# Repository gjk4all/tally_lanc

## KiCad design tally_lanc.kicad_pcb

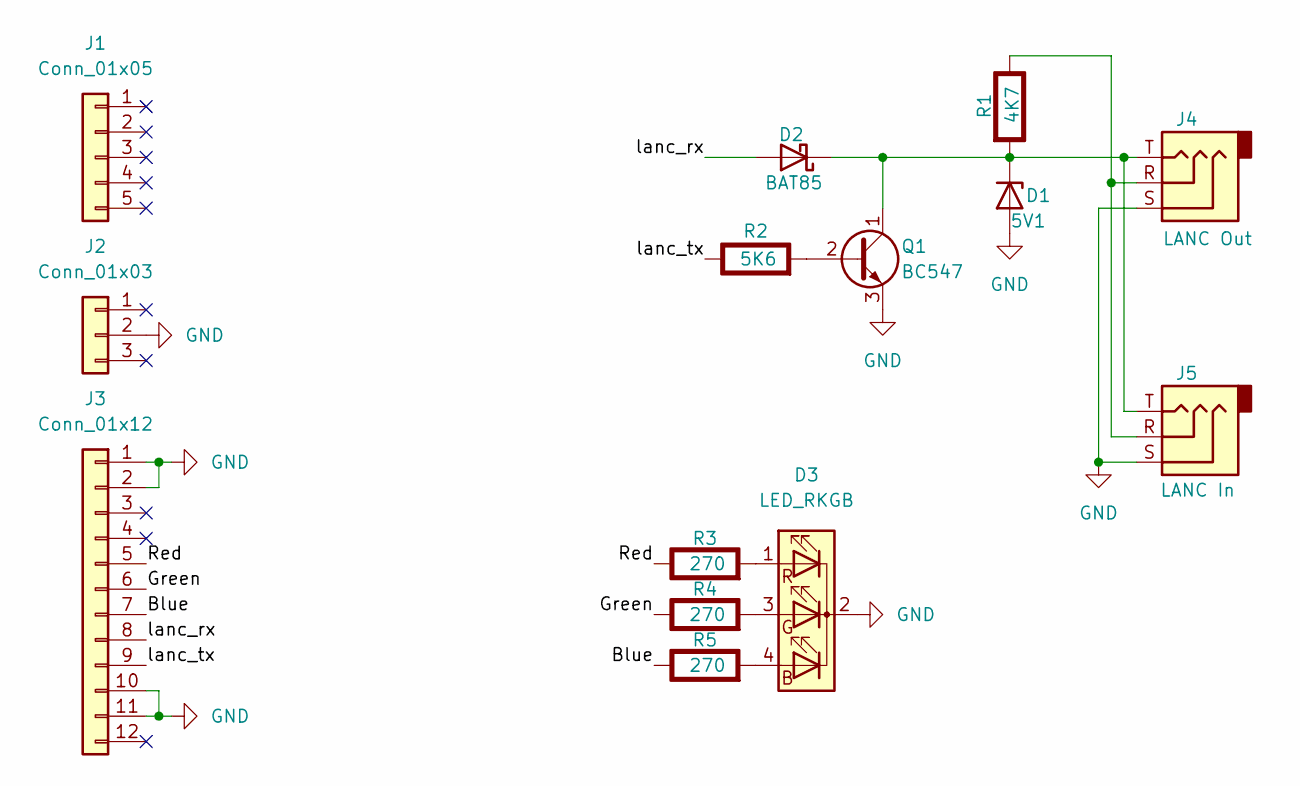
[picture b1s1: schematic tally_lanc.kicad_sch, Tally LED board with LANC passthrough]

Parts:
D1: 5V1; D_A-405_P7.62mm_Horizontal
D2: BAT85; D_DO-35_SOD27_P7.62mm_Horizontal
D3: LED_RKGB; LED_D10.0mm-4
J1: Conn_01x05; PinHeader_1x05_P2.54mm_Vertical
J2: Conn_01x03; PinHeader_1x03_P2.54mm_Vertical
J3: Conn_01x12; PinHeader_1x12_P2.54mm_Vertical
J4: LANC Out; jack_2.5mm_trs_smd
J5: LANC In; jack_2.5mm_trs_smd
Q1: BC547; TO-92_Inline
R1: 4K7; R_Axial_DIN0207_L6.3mm_D2.5mm_P10.16mm_Horizontal; Rating W
R2: 5K6; R_Axial_DIN0207_L6.3mm_D2.5mm_P10.16mm_Horizontal; Rating W
R3, R4, R5: 270; R_Axial_DIN0207_L6.3mm_D2.5mm_P10.16mm_Horizontal; Rating W

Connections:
/Blue: J3.7, R5.1 (+)
/Green: J3.6, R4.1 (+)
/Red: J3.5, R3.1 (+)
/lanc_rx: D2.2 (A), J3.8
/lanc_tx: J3.9, R2.1 (+)
GND: D1.2 (A), D3.2 (K), J2.2, J3.1, J3.2, J3.10, J3.11, J4.S, J5.S, Q1.3 (E)
unnamed: D1.1 (K), D2.1 (K), J4.T, J5.T, Q1.1 (C), R1.2 (-)
unnamed: D3.4 (BA), R5.2 (-)
unnamed: D3.3 (GA), R4.2 (-)
unnamed: D3.1 (RA), R3.2 (-)
unnamed: Q1.2 (B), R2.2 (-)
unnamed: J4.R, J5.R, R1.1 (+)

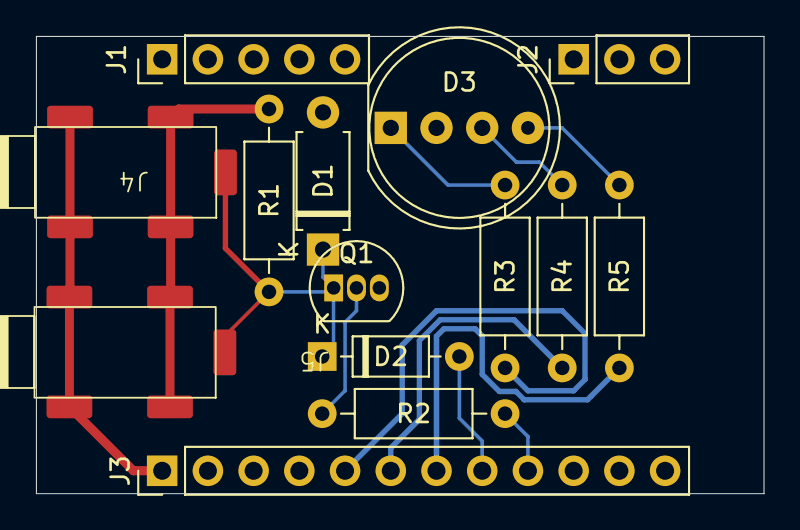
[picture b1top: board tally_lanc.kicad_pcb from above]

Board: 2 copper layers, 40.4 x 25.4 mm, 14 parts (0 on the bottom side), 12 nets.

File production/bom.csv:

Designator,Footprint,Quantity,Value,LCSC Part #
D1,D_A-405_P7.62mm_Horizontal,1,5V1,
D2,D_DO-35_SOD27_P7.62mm_Horizontal,1,BAT85,
D3,LED_D10.0mm-4,1,LED_RKGB,
J1,PinHeader_1x05_P2.54mm_Vertical,1,Conn_01x05,
J2,PinHeader_1x03_P2.54mm_Vertical,1,Conn_01x03,
J3,PinHeader_1x12_P2.54mm_Vertical,1,Conn_01x12,
J4,jack_2.5mm_trs_smd,1,LANC Out,
J5,jack_2.5mm_trs_smd,1,LANC In,
Q1,TO-92_Inline,1,BC547,
R1,R_Axial_DIN0207_L6.3mm_D2.5mm_P10.16mm_Horizontal,1,4K7,
R2,R_Axial_DIN0207_L6.3mm_D2.5mm_P10.16mm_Horizontal,1,5K6,
"R3, R4, R5",R_Axial_DIN0207_L6.3mm_D2.5mm_P10.16mm_Horizontal,3,270,

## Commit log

2025-03-22 Version 1.0
2025-03-23 V2.0
